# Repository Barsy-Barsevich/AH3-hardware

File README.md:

# AH3 hardware repository

- [AH3 on-board software repository](https://github.com/Barsy-Barsevich/AH3-software)
- [AH3 Arduino library](https://github.com/Barsy-Barsevich/AH3_Barsotion)

---
## ⚡️Manual
- [AH3 software 2nd revision manual (newest release)](./Manual/AH3_soft_revision_2_manual.pdf)
- [AH3 software 1st revision manual](./Manual/AH3_soft_revision_1_manual.pdf)
- [AH3 software 1st revision manual (preliminary edition)](./Manual/AH3_soft_revision_1_manual_preliminary_edition.pdf)

---
## ⚡️Previous AHx boards
- [AH1](https://github.com/Barsy-Barsevich/Barsotion-AH1)
- [AH2](https://github.com/Barsy-Barsevich/Barsotion-AH2)

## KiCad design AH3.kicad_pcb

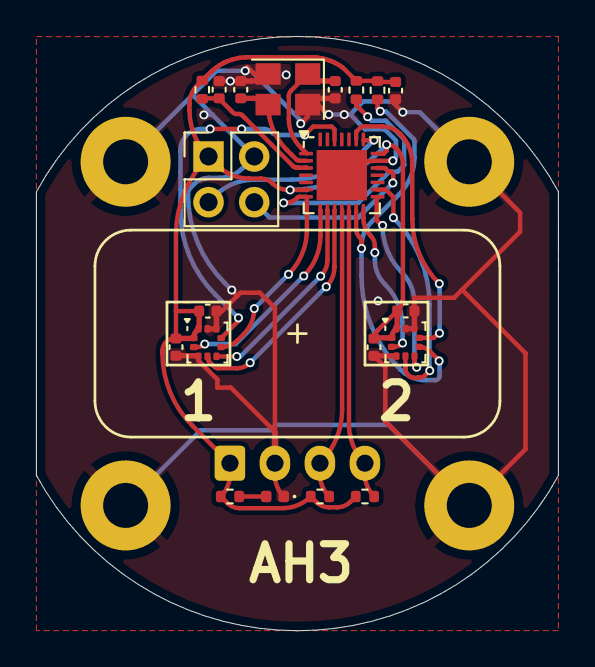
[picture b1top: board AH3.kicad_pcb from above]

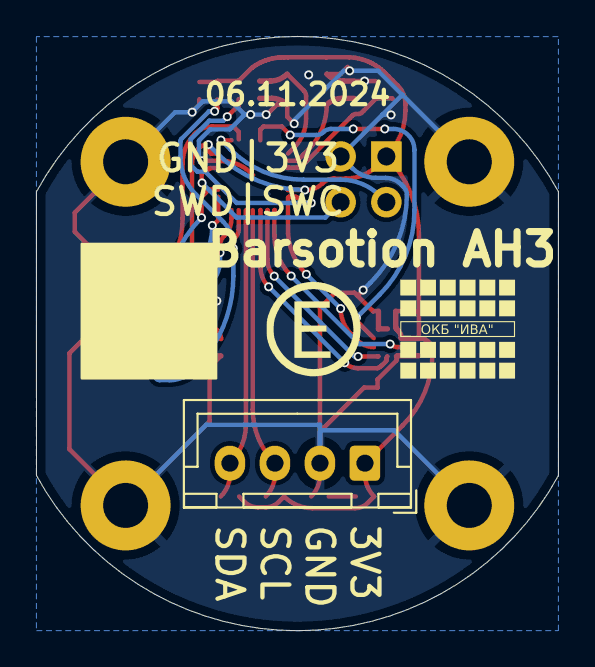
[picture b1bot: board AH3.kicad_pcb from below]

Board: 2 copper layers, 29.0 x 33.0 mm, 25 parts (5 on the bottom side), 20 nets.

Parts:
C1, C2, C3, C4, C7, C8: 0.1uF; C_0402_1005Metric
C5, C6: 12pF; C_0402_1005Metric
D1: Yellow LED; LED_0402_1005Metric
H1, H2, H3, H4: MountingHole_Pad; MountingHole_2.5mm_Pad
J1: PROG; PinHeader_2x02_P2.54mm_Vertical
J3: I2C; JST_XH_B4B-XH-A_1x04_P2.50mm_Vertical
R1, R2, R3, R4, R5: 10k; R_0402_1005Metric
R6: 1k; R_0402_1005Metric
U1, U2: BMP388
U3: CH32V305GBU6; QFN-28-1EP_4x4mm_P0.4mm_EP2.8x2.8mm
Y1: 8MHz; Crystal_SMD_3225-4Pin_3.2x2.5mm

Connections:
/INT1: U1.7 (INT), U3.26 (PD2/UART5RX/SD_CMD)
/INT2: U2.7 (INT), U3.23 (PC10/UART4TX/SPI3SCK1/SD_D2)
/MISO1: U1.5 (SDO), U3.9 (PA6/SPI1MISO)
/MISO2: U2.5 (SDO), U3.15 (PB14/SPI2MISO/UART3RTS)
/MOSI1: U1.4 (SDI/SDA), U3.10 (PA7/SPI1MOSI)
/MOSI2: U2.4 (SDI/SDA), U3.16 (PB15/SPI2MOSI/UART1TX2)
/NSS1: R1.1, U1.6 (CSB), U3.7 (PA4/SPI1NSS/SPI3NSS1/PA1)
/NSS2: R2.1, U2.6 (CSB), U3.13 (PB12/SPI2NSS/CAN2RX)
/SCK1: U1.2 (SCK/SCL), U3.8 (PA5/SPI1SCK)
/SCK2: U2.2 (SCK/SCL), U3.14 (PB13/SPI2SCK/UART3CTS/CAN2TX)
/SCL: J3.3, R4.1, U3.11 (PB10/UART3TX/I2C2SCL)
/SDA: J3.4, R5.1, U3.12 (PB11/UART3RX/I2C2SDA)
/SWCLK: J1.3, U3.22 (PA14/SWCLK/UART3RX2)
/SWDIO: J1.4, U3.19 (PA13/SWDIO/UART3TX2)
GND: C1.2, C2.2, C3.2, C4.2, C5.2, C6.2, C7.2, C8.2, D1.1 (K), H1.1, H2.1, H3.1, H4.1, J1.2, J3.2, U1.3 (VSS), U1.8 (VSS), U1.9 (VSS), U2.3 (VSS), U2.8 (VSS), U2.9 (VSS), U3.20 (VSS/GND), U3.29 (PAD), Y1.2, Y1.4
unnamed: D1.2 (A), R6.1
unnamed: C7.1, R3.1, U3.3 (NRST)
unnamed: C5.1, U3.1 (OCS_IN/PD0), Y1.1
unnamed: C6.1, U3.2 (OCS_OUT/PD1), Y1.3
VDD: C1.1, C2.1, C3.1, C4.1, C8.1, J1.1, J3.1, R1.2, R2.2, R3.2, R4.2, R5.2, R6.2, U1.1 (VDDIO), U1.10 (VDD), U2.1 (VDDIO), U2.10 (VDD), U3.6 (VIO), U3.21 (VDD)

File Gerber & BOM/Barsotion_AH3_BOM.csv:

Reference,Value,Datasheet,Footprint,Qty,DNP
"C1,C2,C3,C4,C7,C8",0.1uF,~,Capacitor_SMD:C_0402_1005Metric,6,
"C5,C6",12pF,~,Capacitor_SMD:C_0402_1005Metric,2,
D1,Yellow LED,~,LED_SMD:LED_0402_1005Metric,1,
"R1,R2,R3,R4,R5",10k,~,Resistor_SMD:R_0402_1005Metric,5,
R6,1k,~,Resistor_SMD:R_0402_1005Metric,1,
"U1,U2",BMP388,https://pdf1.alldatasheet.com/datasheet-pdf/download/1132070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,CustomPackage:BMP388,2,
U3,CH32V305GBU6,,Package_DFN_QFN:QFN-28-1EP_4x4mm_P0.4mm_EP2.8x2.8mm,1,
Y1,8MHz,https://www.lcsc.com/datasheet/lcsc_datasheet_2403291505_YXC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,Crystal:Crystal_SMD_3225-4Pin_3.2x2.5mm,1,

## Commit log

2025-02-22 gitignore creation
2025-03-10 Create LICENSE
2025-03-10 gitignore update
2025-03-10 readme update
2025-04-23 topology photoes added
2025-06-30 2nd revision manual addition
2025-06-30 2nd manual update
2025-11-22 removing local backups
2025-11-22 actual schematic addition
2025-11-22 adding actual BOM
2025-11-22 kicad files addition
2025-11-22 adding pindefs file
2026-01-01 title photo added
